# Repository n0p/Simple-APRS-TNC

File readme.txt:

Simple inexpensive APRS TNC/beacon based on wb8wga's one

Update: It works! :D
http://imgur.com/mMHwAuk
http://imgur.com/1EDHPSL

Original work I adapted: http://www.enide.net/webcms/index.php?page=wb8wga-tnc

This device works as a stand alone configurable APRS beacon/digipeater and also as a serial to APRS terminal. Go to wb8wga's website to find more about it.

I scaled everything into SMD to make it as small as possible, removed the MAX232, as I intend to use this on embedded TTL devices and also I removed the connectors and left it as pin rows, also to embed it / save space.

3x05Ball.zip is the original TNC firmware, on which the wb8wga one is based, it should be compatible and make this board work as a standard APRS TNC.
I upload it here as is a bit hard to find, but I claim no ownership over it.

Disclaimer: 
This is my first EAGLE circuit, so be gentle with me xD

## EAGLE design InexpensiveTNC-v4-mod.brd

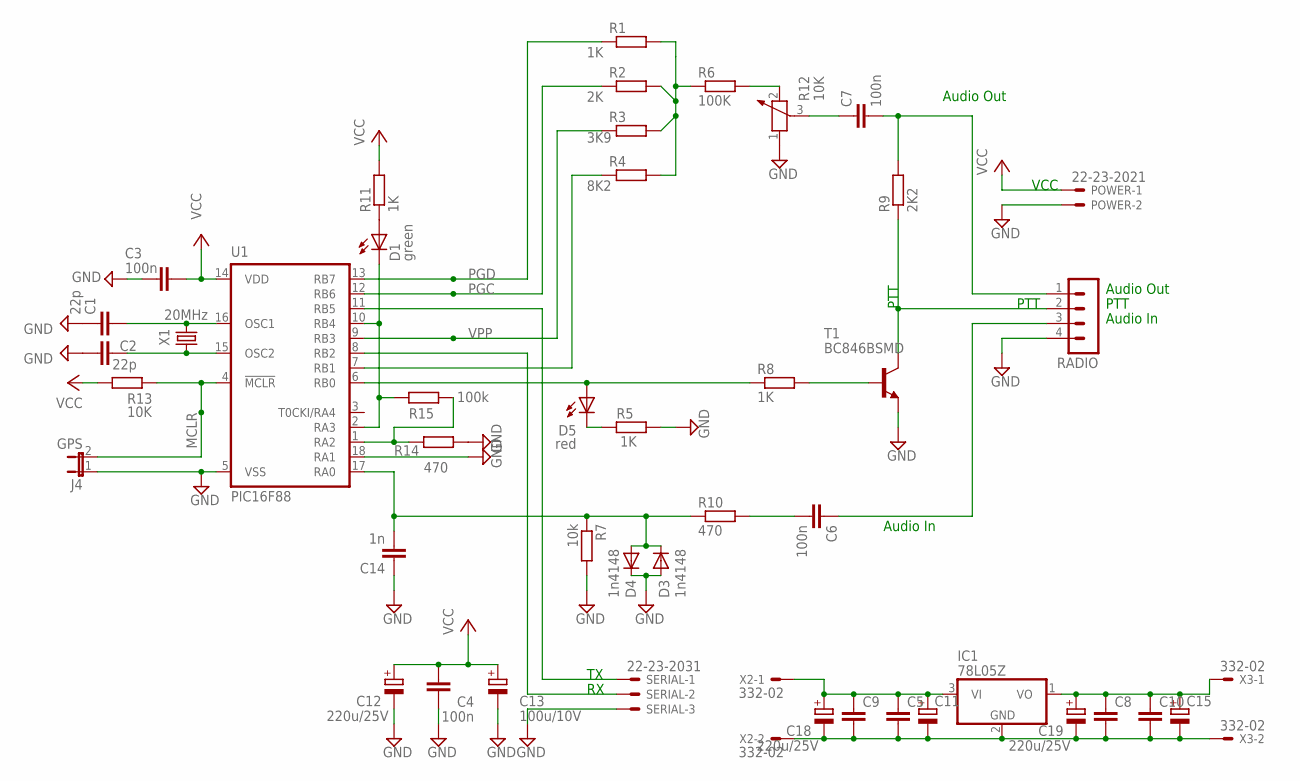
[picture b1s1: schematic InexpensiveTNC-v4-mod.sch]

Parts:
C1, C2: 22p; C0805
C3, C4, C6, C7: 100n; C0805
C5, C8: C-EU025-025X050; C025-025X050
C9, C10: C-EUC0805K; C0805K
C11, C15: CPOL-EUE3.5-10; E3,5-10
C12, C18, C19: 220u/25V; PANASONIC_A
C13: 100u/10V; PANASONIC_A
C14: 1n; C0805
D1: green; CHIPLED_1206
D3, D4: 1n4148; MINIMELF
D5: red; CHIPLED_1206
IC1: 78L05Z; TO92
J4: GPS; JP1
POWER: 22-23-2021
R1, R5, R8, R11: 1K; R0805W
R2: 2K; R0805W
R3: 3K9; R0805W
R4: 8K2; R0805W
R6: 100K; R0805W
R7: 10k; R0805W
R9: 2K2; R0805W
R10, R14: 470; R0805W
R12: 10K; PT-10S
R13: 10K; R0805W
R15: 100k; R0805W
RADIO: MA04-1
SERIAL: 22-23-2031
T1: BC846BSMD; SOT23
U1: PIC16F88; SO-18W; MPN PIC16F83-04/SO
X1: 20MHz; HC49U70
X2, X3: 332-02

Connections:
GND: C1.1, C2.1, C3.2, C4.1, C12.-, C13.-, C14.1, D3.A, D4.C, J4.1, POWER.2, R5.2, R7.2, R12.1, R14.2, RADIO.4, SERIAL.3, T1.2 (E), U1.5 (VSS), U1.18 (RA1)
MCLR: J4.2, R13.2, U1.4 (!MCLR)
unnamed: C1.2, U1.16 (OSC1), X1.2
unnamed: C2.2, U1.15 (OSC2), X1.1
unnamed: D1.A, R11.1
unnamed: R4.1, U1.7 (RB1)
unnamed: D1.C, R15.2, U1.2 (RA3), U1.10 (RB4)
unnamed: R8.2, T1.1 (B)
unnamed: R1.2, R2.2, R3.2, R4.2, R6.1
unnamed: R6.2, R12.2
unnamed: C7.1, R12.3
unnamed: D5.A, R8.1, U1.6 (RB0)
unnamed: D5.C, R5.1
unnamed: R9.1, RADIO.2, T1.3 (C)
unnamed: C7.2, R9.2, RADIO.1
unnamed: C14.2, D3.C, D4.A, R7.1, R10.1, U1.17 (RA0)
unnamed: C6.2, R10.2
unnamed: R14.1, R15.1, U1.1 (RA2)
unnamed: C6.1, RADIO.3
unnamed: SERIAL.1, U1.11 (RB5)
unnamed: SERIAL.2, U1.8 (RB2)
PGC: R2.1, U1.12 (RB6)
PGD: R1.1, U1.13 (RB7)
VCC: C3.1, C4.2, C12.+, C13.+, POWER.1, R11.2, R13.1, U1.14 (VDD)
VPP: R3.1, U1.9 (RB3)
VREG-GND: C5.2, C8.2, C9.2, C10.2, C11.-, C15.-, C18.-, C19.-, IC1.2 (GND), X2.2, X3.2
VREG-VIN: C5.1, C9.1, C11.+, C18.+, IC1.3 (VI), X2.1
VREG-VOUT: C8.1, C10.1, C15.+, C19.+, IC1.1 (VO), X3.1

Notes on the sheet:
Audio Out
PTT
Audio In
VCC

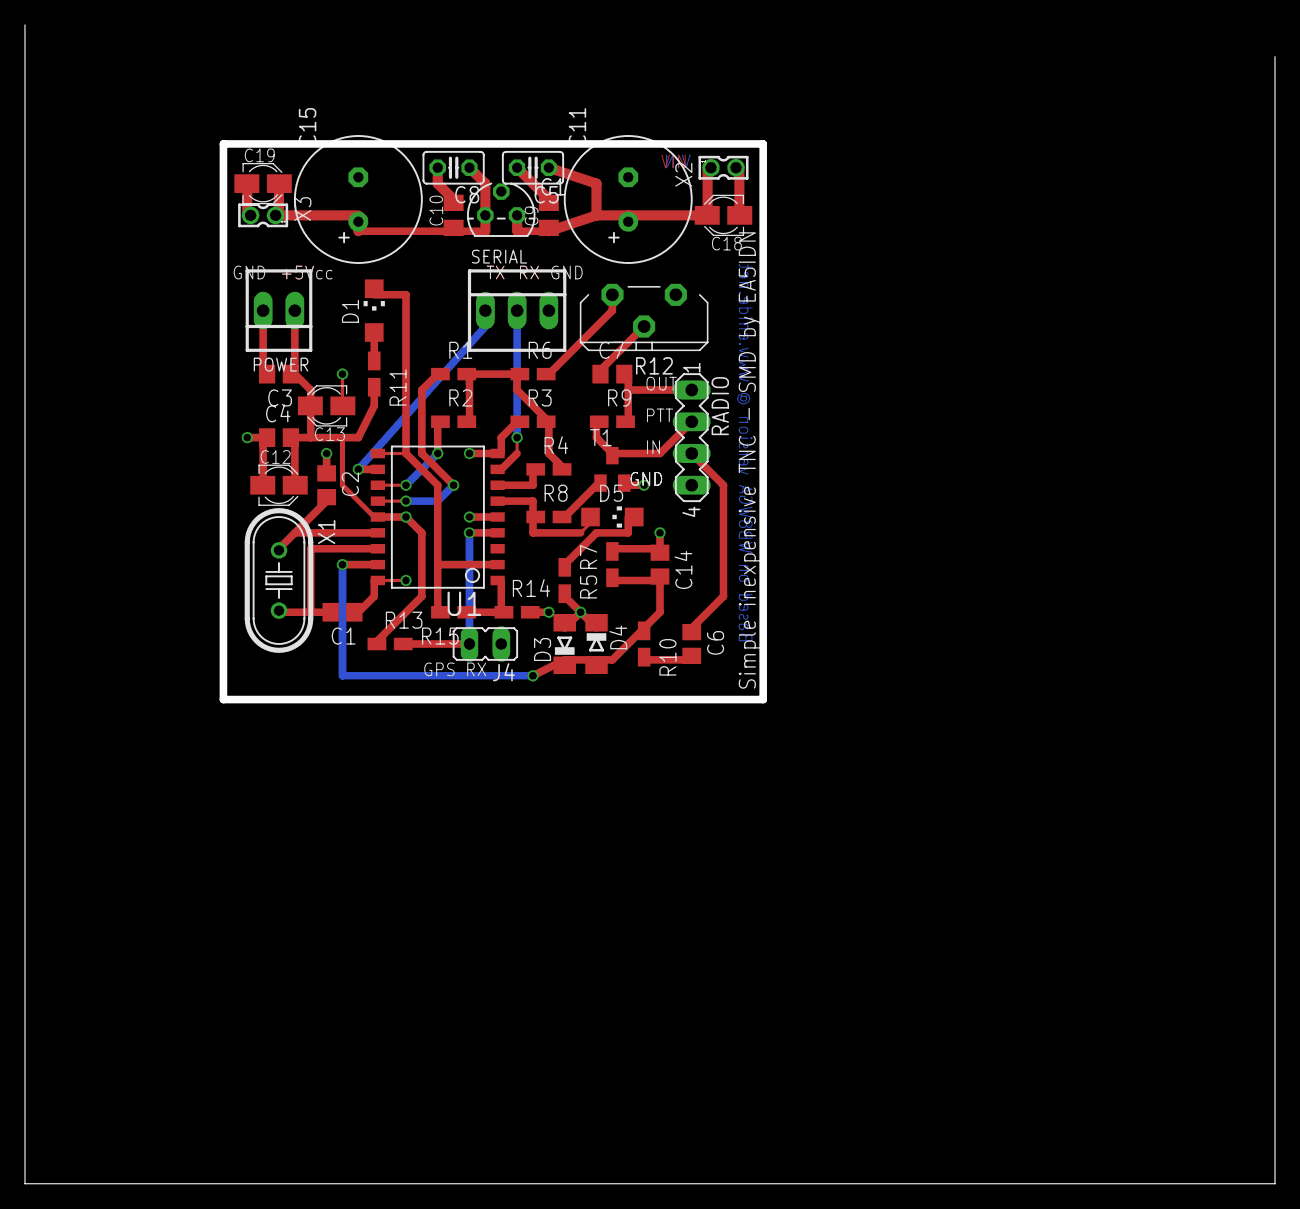
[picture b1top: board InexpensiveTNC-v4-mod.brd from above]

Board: 2 copper layers, 99.4 x 92.1 mm, 46 parts (0 on the bottom side), 28 nets.

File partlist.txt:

Partlist

Exported from InexpensiveTNC-v4-mod.sch at 9/5/15 3:22 AM

EAGLE Version 7.4.0 Copyright (c) 1988-2015 CadSoft

Assembly variant: 

Part     Value          Device               Package      Library        Sheet

C1       22p            C-EUC0805            C0805        rcl            1
C2       22p            C-EUC0805            C0805        rcl            1
C3       100n           C-EUC0805            C0805        rcl            1
C4       100n           C-EUC0805            C0805        rcl            1
C5                      C-EU025-025X050      C025-025X050 rcl            1
C6       100n           C-EUC0805            C0805        rcl            1
C7       100n           C-EUC0805            C0805        rcl            1
C8                      C-EU025-025X050      C025-025X050 rcl            1
C9                      C-EUC0805K           C0805K       rcl            1
C10                     C-EUC0805K           C0805K       rcl            1
C11                     CPOL-EUE3.5-10       E3,5-10      rcl            1
C12      220u/25V       CPOL-EUA             PANASONIC_A  rcl            1
C13      100u/10V       CPOL-EUA             PANASONIC_A  rcl            1
C14      1n             C-EUC0805            C0805        rcl            1
C15                     CPOL-EUE3.5-10       E3,5-10      rcl            1
C18      220u/25V       CPOL-EUA             PANASONIC_A  rcl            1
C19      220u/25V       CPOL-EUA             PANASONIC_A  rcl            1
D1       green          LEDCHIPLED_1206      CHIPLED_1206 led            1
D3       1n4148         DIODE-MINIMELF       MINIMELF     diode          1
D4       1n4148         DIODE-MINIMELF       MINIMELF     diode          1
D5       red            LEDCHIPLED_1206      CHIPLED_1206 led            1
IC1      78L05Z         78L05Z               TO92         linear         1
J4       GPS            JP1E                 JP1          jumper         1
POWER    22-23-2021     22-23-2021           22-23-2021   con-molex      1
R1       1K             R-EU_R0805W          R0805W       rcl            1
R2       2K             R-EU_R0805W          R0805W       rcl            1
R3       3K9            R-EU_R0805W          R0805W       rcl            1
R4       8K2            R-EU_R0805W          R0805W       rcl            1
R5       1K             R-EU_R0805W          R0805W       rcl            1
R6       100K           R-EU_R0805W          R0805W       rcl            1
R7       10k            R-EU_R0805W          R0805W       rcl            1
R8       1K             R-EU_R0805W          R0805W       rcl            1
R9       2K2            R-EU_R0805W          R0805W       rcl            1
R10      470            R-EU_R0805W          R0805W       rcl            1
R11      1K             R-EU_R0805W          R0805W       rcl            1
R12      10K            POTENTIOMETER_PT-10S PT-10S       rcl            1
R13      10K            R-EU_R0805W          R0805W       rcl            1
R14      470            R-EU_R0805W          R0805W       rcl            1
R15      100k           R-EU_R0805W          R0805W       rcl            1
RADIO                   MA04-1               MA04-1       con-lstb       1
SERIAL   22-23-2031     22-23-2031           22-23-2031   con-molex      1
T1       BC846BSMD      BC846BSMD            SOT23        transistor-npn 1
U1       PIC16F88       PIC16F83SO           SO-18W       microchip      1
X1       20MHz          CRYSTALHC49U70       HC49U70      crystal        1
X2       332-02         332-02               332-02       con-garry      1
X3       332-02         332-02               332-02       con-garry      1

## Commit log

2013-08-28 Added n00b disclaimer xD
2013-08-29 Traces widened, generated some gerblers for ITEAD studio
2014-03-31 Update readme.txt
    It works! :D
2015-09-06 Added partlist
